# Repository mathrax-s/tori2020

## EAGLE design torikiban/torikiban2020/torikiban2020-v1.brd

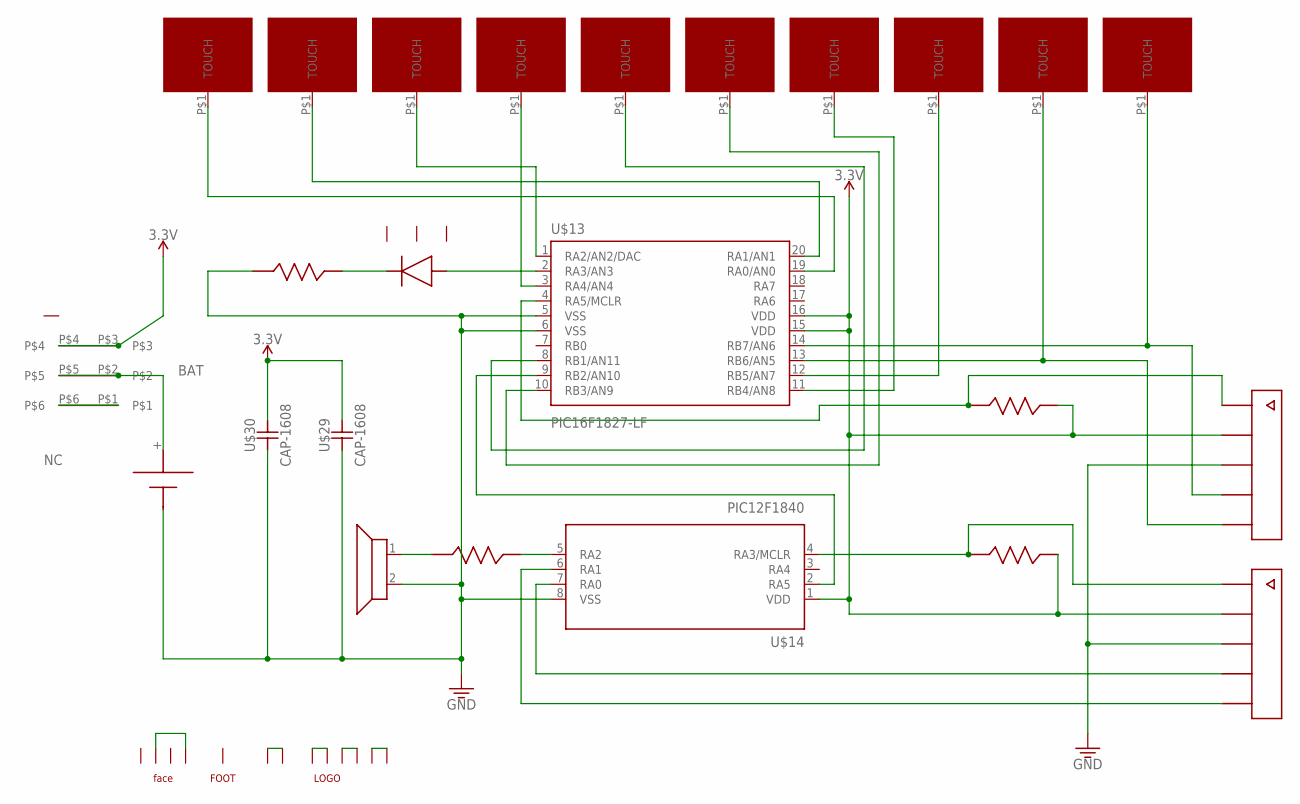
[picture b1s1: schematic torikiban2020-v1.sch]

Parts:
U$1: TOUCH-PTN-H1; HANE-1
U$2: TOUCH-PTN-H2; HANE-2
U$3: TOUCH-PTN-H3; HANE-3
U$4: TOUCH-PTN-H4; HANE-4
U$5: TOUCH-PTN-H5; HANE-5
U$6: TOUCH-PTN-H6; HANE-6
U$7: TOUCH-PTN-H7; HANE-7
U$8: TOUCH-PTN-H8; HANE-8
U$9: TOUCH-PTN-H9; HANE-9
U$10: TOUCH-PTN-H10; HANE-10
U$13: PIC16F1827-LF; SSOP20
U$14: PIC12F1840; SOIC127P600X175-8N
U$15: FACE
U$16: SPEAKER
U$17: FACE-LED
U$18, U$19, U$20, U$22: RESISTOR-1608; RESC1608X70N
U$21: ICSP-2X
U$24: PAD-FOOT
U$25: CR2032-TAKACHI
U$26: MLOGO
U$27: SWITCH; SSSS213202
U$29, U$30: CAP-1608

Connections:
3.3V: U$13.15 (VDD), U$13.16 (VDD), U$14.1 (VDD), U$19.2, U$20.2, U$21.P$2 (2), U$21.P$7 (7), U$27.P$3, U$27.P$4, U$29.2, U$30.2
BAT: U$25.+, U$27.P$2, U$27.P$5
GND: U$13.5 (VSS), U$13.6 (VSS), U$14.8 (VSS), U$16.2, U$18.1, U$21.P$3 (3), U$21.P$8 (8), U$25.-, U$29.1, U$30.1
unnamed: U$15.P$2 (2), U$15.P$4 (4)
unnamed: U$1.P$1, U$13.19 (RA0/AN0)
unnamed: U$2.P$1, U$13.20 (RA1/AN1)
unnamed: U$13.2 (RA3/AN3), U$17.1
unnamed: U$17.2, U$18.2
unnamed: U$6.P$1, U$13.10 (RB3/AN9)
unnamed: U$3.P$1, U$13.1 (RA2/AN2/DAC)
unnamed: U$4.P$1, U$13.3 (RA4/AN4)
unnamed: U$13.9 (RB2/AN10), U$14.2 (RA5)
unnamed: U$5.P$1, U$13.8 (RB1/AN11)
unnamed: U$7.P$1, U$13.11 (RB4/AN8)
unnamed: U$8.P$1, U$13.12 (RB5/AN7)
unnamed: U$9.P$1, U$13.13 (RB6/AN5), U$21.P$5 (5)
unnamed: U$10.P$1, U$13.14 (RB7/AN6), U$21.P$4 (4)
unnamed: U$14.5 (RA2), U$22.2
unnamed: U$16.1, U$22.1
unnamed: U$14.4 (RA3/MCLR), U$20.1, U$21.P$6 (6)
unnamed: U$14.6 (RA1), U$21.P$10 (10)
unnamed: U$14.7 (RA0), U$21.P$9 (9)
unnamed: U$13.4 (RA5/MCLR), U$19.1, U$21.P$1 (1)
unnamed: U$26.1, U$26.2
unnamed: U$26.A1, U$26.A2
unnamed: U$26.R1, U$26.R2
unnamed: U$26.A3, U$26.A4
NC: U$27.P$1, U$27.P$6

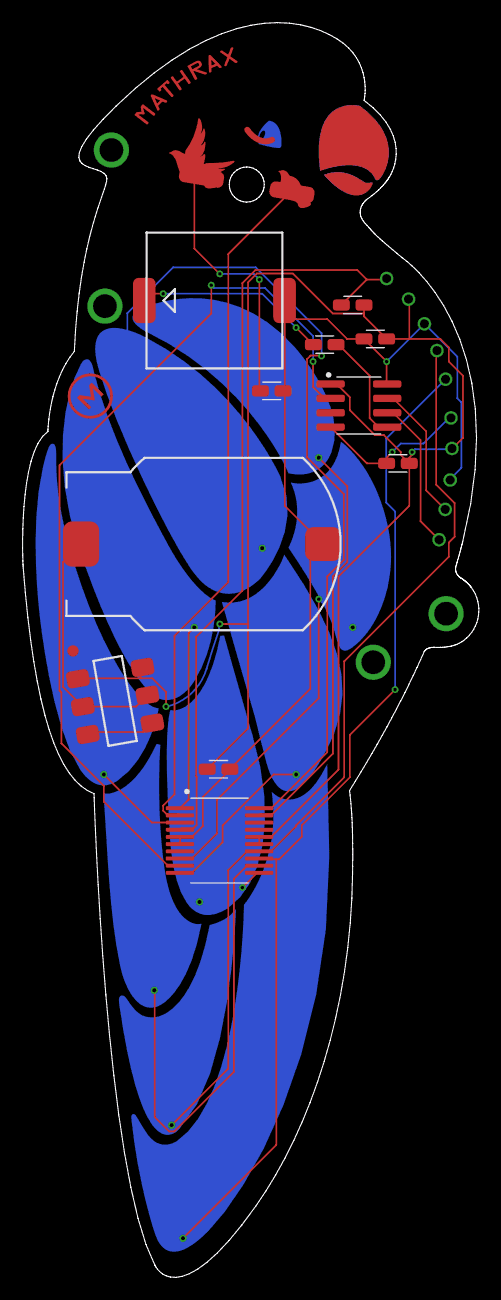
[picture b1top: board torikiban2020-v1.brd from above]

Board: 2 copper layers, 40.3 x 110.9 mm, 26 parts (0 on the bottom side), 28 nets.

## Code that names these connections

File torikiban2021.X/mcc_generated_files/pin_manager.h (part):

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#define RA0_SetHigh()            do { LATAbits.LATA0 = 1; } while(0)
#define RA0_SetLow()             do { LATAbits.LATA0 = 0; } while(0)
#define RA0_Toggle()             do { LATAbits.LATA0 = ~LATAbits.LATA0; } while(0)
#define RA0_GetValue()              PORTAbits.RA0
#define RA0_SetDigitalInput()    do { TRISAbits.TRISA0 = 1; } while(0)
#define RA0_SetDigitalOutput()   do { TRISAbits.TRISA0 = 0; } while(0)
#define RA0_SetAnalogMode()         do { ANSELAbits.ANSA0 = 1; } while(0)
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#define RA1_SetHigh()            do { LATAbits.LATA1 = 1; } while(0)
#define RA1_SetLow()             do { LATAbits.LATA1 = 0; } while(0)
#define RA1_Toggle()             do { LATAbits.LATA1 = ~LATAbits.LATA1; } while(0)
#define RA1_GetValue()              PORTAbits.RA1
#define RA1_SetDigitalInput()    do { TRISAbits.TRISA1 = 1; } while(0)
#define RA1_SetDigitalOutput()   do { TRISAbits.TRISA1 = 0; } while(0)
#define RA1_SetAnalogMode()         do { ANSELAbits.ANSA1 = 1; } while(0)
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#define RA2_SetHigh()            do { LATAbits.LATA2 = 1; } while(0)
#define RA2_SetLow()             do { LATAbits.LATA2 = 0; } while(0)
#define RA2_Toggle()             do { LATAbits.LATA2 = ~LATAbits.LATA2; } while(0)
#define RA2_GetValue()              PORTAbits.RA2
#define RA2_SetDigitalInput()    do { TRISAbits.TRISA2 = 1; } while(0)
#define RA2_SetDigitalOutput()   do { TRISAbits.TRISA2 = 0; } while(0)
#define RA2_SetAnalogMode()         do { ANSELAbits.ANSA2 = 1; } while(0)
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// get/set LED aliases
#define LED_TRIS                 TRISAbits.TRISA3
#define LED_LAT                  LATAbits.LATA3
#define LED_PORT                 PORTAbits.RA3
#define LED_ANS                  ANSELAbits.ANSA3
#define LED_SetHigh()            do { LATAbits.LATA3 = 1; } while(0)
#define LED_SetLow()             do { LATAbits.LATA3 = 0; } while(0)
#define LED_Toggle()             do { LATAbits.LATA3 = ~LATAbits.LATA3; } while(0)
#define LED_GetValue()           PORTAbits.RA3
#define LED_SetDigitalInput()    do { TRISAbits.TRISA3 = 1; } while(0)
#define LED_SetDigitalOutput()   do { TRISAbits.TRISA3 = 0; } while(0)
#define LED_SetAnalogMode()      do { ANSELAbits.ANSA3 = 1; } while(0)
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#define RA4_SetHigh()            do { LATAbits.LATA4 = 1; } while(0)
#define RA4_SetLow()             do { LATAbits.LATA4 = 0; } while(0)
#define RA4_Toggle()             do { LATAbits.LATA4 = ~LATAbits.LATA4; } while(0)
#define RA4_GetValue()              PORTAbits.RA4
#define RA4_SetDigitalInput()    do { TRISAbits.TRISA4 = 1; } while(0)
#define RA4_SetDigitalOutput()   do { TRISAbits.TRISA4 = 0; } while(0)
#define RA4_SetAnalogMode()         do { ANSELAbits.ANSA4 = 1; } while(0)
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#define RB1_SetHigh()            do { LATBbits.LATB1 = 1; } while(0)
#define RB1_SetLow()             do { LATBbits.LATB1 = 0; } while(0)
#define RB1_Toggle()             do { LATBbits.LATB1 = ~LATBbits.LATB1; } while(0)
#define RB1_GetValue()              PORTBbits.RB1
#define RB1_SetDigitalInput()    do { TRISBbits.TRISB1 = 1; } while(0)
#define RB1_SetDigitalOutput()   do { TRISBbits.TRISB1 = 0; } while(0)
#define RB1_SetPullup()             do { WPUBbits.WPUB1 = 1; } while(0)
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#define RB2_SetHigh()            do { LATBbits.LATB2 = 1; } while(0)
#define RB2_SetLow()             do { LATBbits.LATB2 = 0; } while(0)
#define RB2_Toggle()             do { LATBbits.LATB2 = ~LATBbits.LATB2; } while(0)
#define RB2_GetValue()              PORTBbits.RB2
#define RB2_SetDigitalInput()    do { TRISBbits.TRISB2 = 1; } while(0)
#define RB2_SetDigitalOutput()   do { TRISBbits.TRISB2 = 0; } while(0)
#define RB2_SetPullup()             do { WPUBbits.WPUB2 = 1; } while(0)
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#define RB3_SetHigh()            do { LATBbits.LATB3 = 1; } while(0)
#define RB3_SetLow()             do { LATBbits.LATB3 = 0; } while(0)
#define RB3_Toggle()             do { LATBbits.LATB3 = ~LATBbits.LATB3; } while(0)
#define RB3_GetValue()              PORTBbits.RB3
#define RB3_SetDigitalInput()    do { TRISBbits.TRISB3 = 1; } while(0)
#define RB3_SetDigitalOutput()   do { TRISBbits.TRISB3 = 0; } while(0)
#define RB3_SetPullup()             do { WPUBbits.WPUB3 = 1; } while(0)
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#define RB4_SetHigh()            do { LATBbits.LATB4 = 1; } while(0)
#define RB4_SetLow()             do { LATBbits.LATB4 = 0; } while(0)
#define RB4_Toggle()             do { LATBbits.LATB4 = ~LATBbits.LATB4; } while(0)
#define RB4_GetValue()              PORTBbits.RB4
#define RB4_SetDigitalInput()    do { TRISBbits.TRISB4 = 1; } while(0)
#define RB4_SetDigitalOutput()   do { TRISBbits.TRISB4 = 0; } while(0)
#define RB4_SetPullup()             do { WPUBbits.WPUB4 = 1; } while(0)
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#define RB5_SetHigh()            do { LATBbits.LATB5 = 1; } while(0)
#define RB5_SetLow()             do { LATBbits.LATB5 = 0; } while(0)
#define RB5_Toggle()             do { LATBbits.LATB5 = ~LATBbits.LATB5; } while(0)
#define RB5_GetValue()              PORTBbits.RB5
#define RB5_SetDigitalInput()    do { TRISBbits.TRISB5 = 1; } while(0)
#define RB5_SetDigitalOutput()   do { TRISBbits.TRISB5 = 0; } while(0)
#define RB5_SetPullup()             do { WPUBbits.WPUB5 = 1; } while(0)
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#define RB6_SetHigh()            do { LATBbits.LATB6 = 1; } while(0)
#define RB6_SetLow()             do { LATBbits.LATB6 = 0; } while(0)
#define RB6_Toggle()             do { LATBbits.LATB6 = ~LATBbits.LATB6; } while(0)
#define RB6_GetValue()              PORTBbits.RB6
#define RB6_SetDigitalInput()    do { TRISBbits.TRISB6 = 1; } while(0)
#define RB6_SetDigitalOutput()   do { TRISBbits.TRISB6 = 0; } while(0)
#define RB6_SetPullup()             do { WPUBbits.WPUB6 = 1; } while(0)
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#define RB7_SetHigh()            do { LATBbits.LATB7 = 1; } while(0)
#define RB7_SetLow()             do { LATBbits.LATB7 = 0; } while(0)
#define RB7_Toggle()             do { LATBbits.LATB7 = ~LATBbits.LATB7; } while(0)
#define RB7_GetValue()              PORTBbits.RB7
#define RB7_SetDigitalInput()    do { TRISBbits.TRISB7 = 1; } while(0)
#define RB7_SetDigitalOutput()   do { TRISBbits.TRISB7 = 0; } while(0)
#define RB7_SetPullup()             do { WPUBbits.WPUB7 = 1; } while(0)
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
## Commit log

2020-05-13 first
2021-07-11 tori2021
2021-07-25 2021_workshop_update

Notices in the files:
torikiban2021.X/mcc_generated_files/pin_manager.h:
(c) 2018 Microchip Technology Inc. and its subsidiaries.
